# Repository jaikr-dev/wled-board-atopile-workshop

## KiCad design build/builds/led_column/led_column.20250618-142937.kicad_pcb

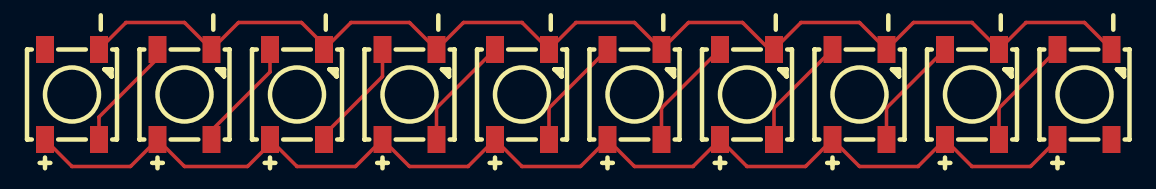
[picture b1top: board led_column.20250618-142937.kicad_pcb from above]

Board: 2 copper layers, 10 parts (0 on the bottom side), 11 nets.

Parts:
LED1, LED2, LED3, LED4, LED5, LED6, LED7, LED8, LED9, LED10: LED-SMD_4P-L5.0-W5.0-BL_XL-5050RGBC

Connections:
DIN: LED2.2, LED3.4
DIN-1: LED7.2, LED8.4
DIN-2: LED1.2, LED2.4
DOU: LED3.2, LED4.4
DOU-1: LED8.2, LED9.4
DOU-2: LED6.2, LED7.4
DOU-3: LED5.2, LED6.4
DOU-4: LED9.2, LED10.4
DOU-5: LED4.2, LED5.4
VDD: LED1.1, LED2.1, LED3.1, LED4.1, LED5.1, LED6.1, LED7.1, LED8.1, LED9.1, LED10.1
gnd: LED1.3, LED2.3, LED3.3, LED4.3, LED5.3, LED6.3, LED7.3, LED8.3, LED9.3, LED10.3
